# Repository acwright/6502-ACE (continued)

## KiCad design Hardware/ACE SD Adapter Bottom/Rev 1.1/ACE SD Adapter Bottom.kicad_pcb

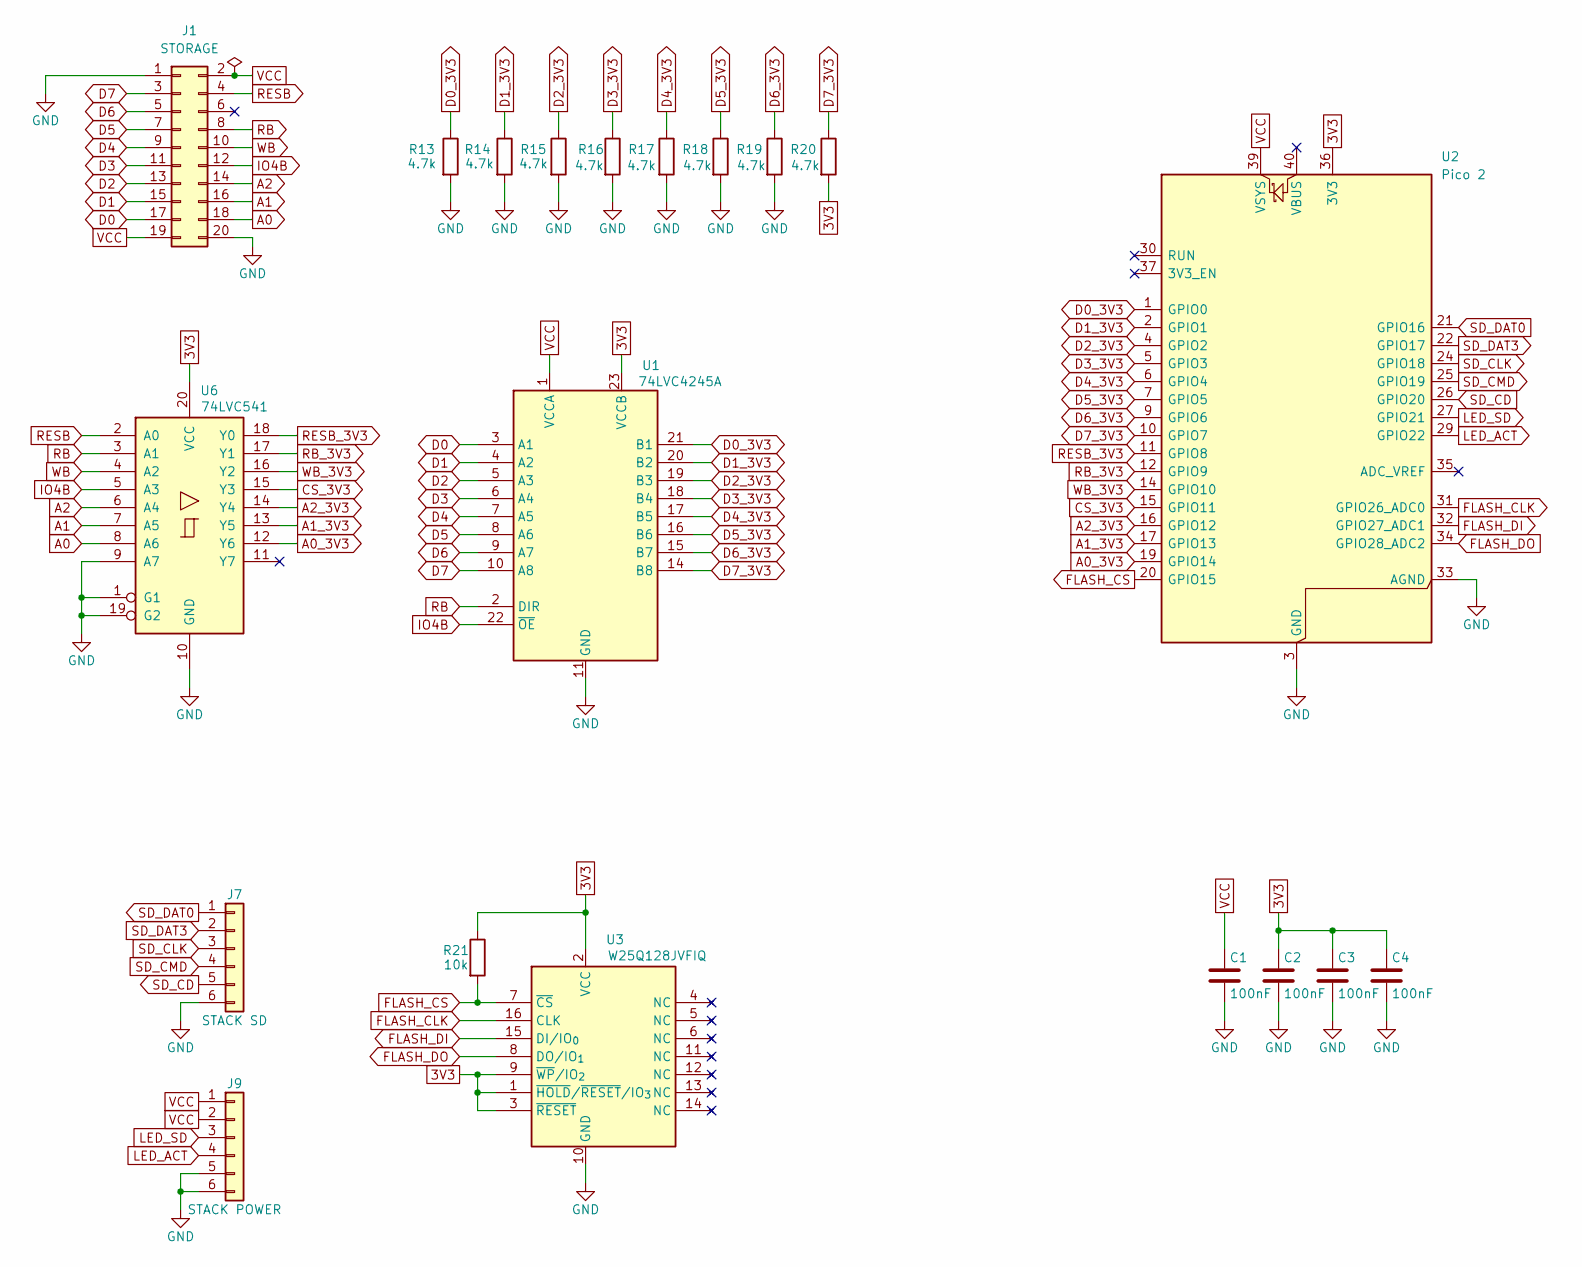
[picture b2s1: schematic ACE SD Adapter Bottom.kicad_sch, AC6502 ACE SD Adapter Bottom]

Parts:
C1, C2, C3, C4: 100nF; C_0805_2012Metric; Digikey 311-1140-1-ND
J1: STORAGE; PinHeader_2x10_P2.54mm_Horizontal; Digikey 609-3338-ND
J7: STACK SD; PinSocket_1x06_P2.54mm_Vertical; Digikey S7004-ND
J9: STACK POWER; PinSocket_1x06_P2.54mm_Vertical; Digikey S7004-ND
R13, R14, R15, R16, R17, R18, R19, R20: 4.7k; R_0805_2012Metric; Digikey 311-4.70KCRCT-ND
R21: 10k; R_0805_2012Metric; Digikey 311-10.0KCRCT-ND
U1: 74LVC4245A; TSSOP-24_4.4x7.8mm_P0.65mm; Digikey 296-12183-1-ND
U2: Pico 2; RaspberryPi_Pico_Common_THT; Digikey 2648-SC1631CT-ND
U3: W25Q128JVFIQ; SOIC-16W_7.5x10.3mm_P1.27mm; Digikey W25Q128JVFIQ-ND
U6: 74LVC541; TSSOP-20_4.4x6.5mm_P0.65mm; Digikey 1727-6370-1-ND

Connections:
3V3: C2.1, C3.1, C4.1, R20.2, R21.1, U1.23 (VCCB), U1.24 (VCCB), U2.36 (3V3), U3.1 (~HOLD/~RESET/IO_{3}), U3.2 (VCC), U3.3 (~RESET), U3.9 (~WP/IO_{2}), U6.20 (VCC)
A0: J1.18, U6.8 (A6)
A0_3V3: U2.19 (GPIO14), U6.12 (Y6)
A1: J1.16, U6.7 (A5)
A1_3V3: U2.17 (GPIO13), U6.13 (Y5)
A2: J1.14, U6.6 (A4)
A2_3V3: U2.16 (GPIO12), U6.14 (Y4)
CS_3V3: U2.15 (GPIO11), U6.15 (Y3)
D0: J1.17, U1.3 (A1)
D0_3V3: R13.1, U1.21 (B1), U2.1 (GPIO0)
D1: J1.15, U1.4 (A2)
D1_3V3: R14.1, U1.20 (B2), U2.2 (GPIO1)
D2: J1.13, U1.5 (A3)
D2_3V3: R15.1, U1.19 (B3), U2.4 (GPIO2)
D3: J1.11, U1.6 (A4)
D3_3V3: R16.1, U1.18 (B4), U2.5 (GPIO3)
D4: J1.9, U1.7 (A5)
D4_3V3: R17.1, U1.17 (B5), U2.6 (GPIO4)
D5: J1.7, U1.8 (A6)
D5_3V3: R18.1, U1.16 (B6), U2.7 (GPIO5)
D6: J1.5, U1.9 (A7)
D6_3V3: R19.1, U1.15 (B7), U2.9 (GPIO6)
D7: J1.3, U1.10 (A8)
D7_3V3: R20.1, U1.14 (B8), U2.10 (GPIO7)
FLASH_CLK: U2.31 (GPIO26_ADC0), U3.16 (CLK)
FLASH_CS: R21.2, U2.20 (GPIO15), U3.7 (~CS)
FLASH_DI: U2.32 (GPIO27_ADC1), U3.15 (DI/IO_{0})
FLASH_DO: U2.34 (GPIO28_ADC2), U3.8 (DO/IO_{1})
GND: C1.2, C2.2, C3.2, C4.2, J1.1, J1.20, J7.6, J9.5, J9.6, R13.2, R14.2, R15.2, R16.2, R17.2, R18.2, R19.2, U1.11 (GND), U1.12 (GND), U1.13 (GND), U2.3 (GND), U2.8 (GND), U2.13 (GND), U2.18 (GND), U2.23 (GND), U2.28 (GND), U2.33 (AGND), U2.38 (GND), U3.10 (GND), U6.1 (G1), U6.9 (A7), U6.10 (GND), U6.19 (G2)
IO4B: J1.12, U1.22 (~OE), U6.5 (A3)
LED_ACT: J9.4, U2.29 (GPIO22)
LED_SD: J9.3, U2.27 (GPIO21)
RB: J1.8, U1.2 (DIR), U6.3 (A1)
RB_3V3: U2.12 (GPIO9), U6.17 (Y1)
RESB: J1.4, U6.2 (A0)
RESB_3V3: U2.11 (GPIO8), U6.18 (Y0)
SD_CD: J7.5, U2.26 (GPIO20)
SD_CLK: J7.3, U2.24 (GPIO18)
SD_CMD: J7.4, U2.25 (GPIO19)
SD_DAT0: J7.1, U2.21 (GPIO16)
SD_DAT3: J7.2, U2.22 (GPIO17)
VCC: C1.1, J1.2, J1.19, J9.1, J9.2, U1.1 (VCCA), U2.39 (VSYS)
WB: J1.10, U6.4 (A2)
WB_3V3: U2.14 (GPIO10), U6.16 (Y2)

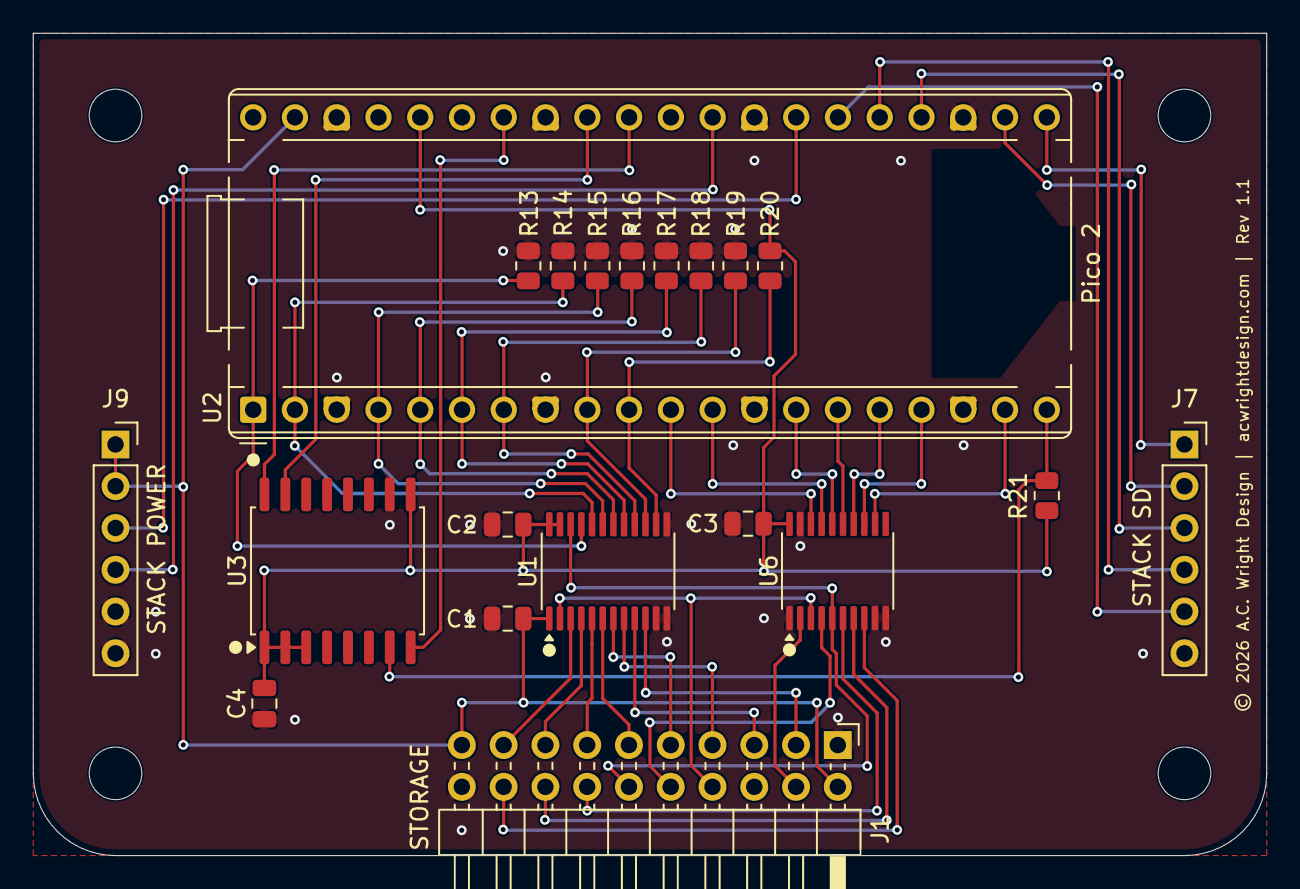
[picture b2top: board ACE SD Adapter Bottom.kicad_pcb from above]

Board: 2 copper layers, 75.0 x 50.0 mm, 20 parts (0 on the bottom side), 44 nets.

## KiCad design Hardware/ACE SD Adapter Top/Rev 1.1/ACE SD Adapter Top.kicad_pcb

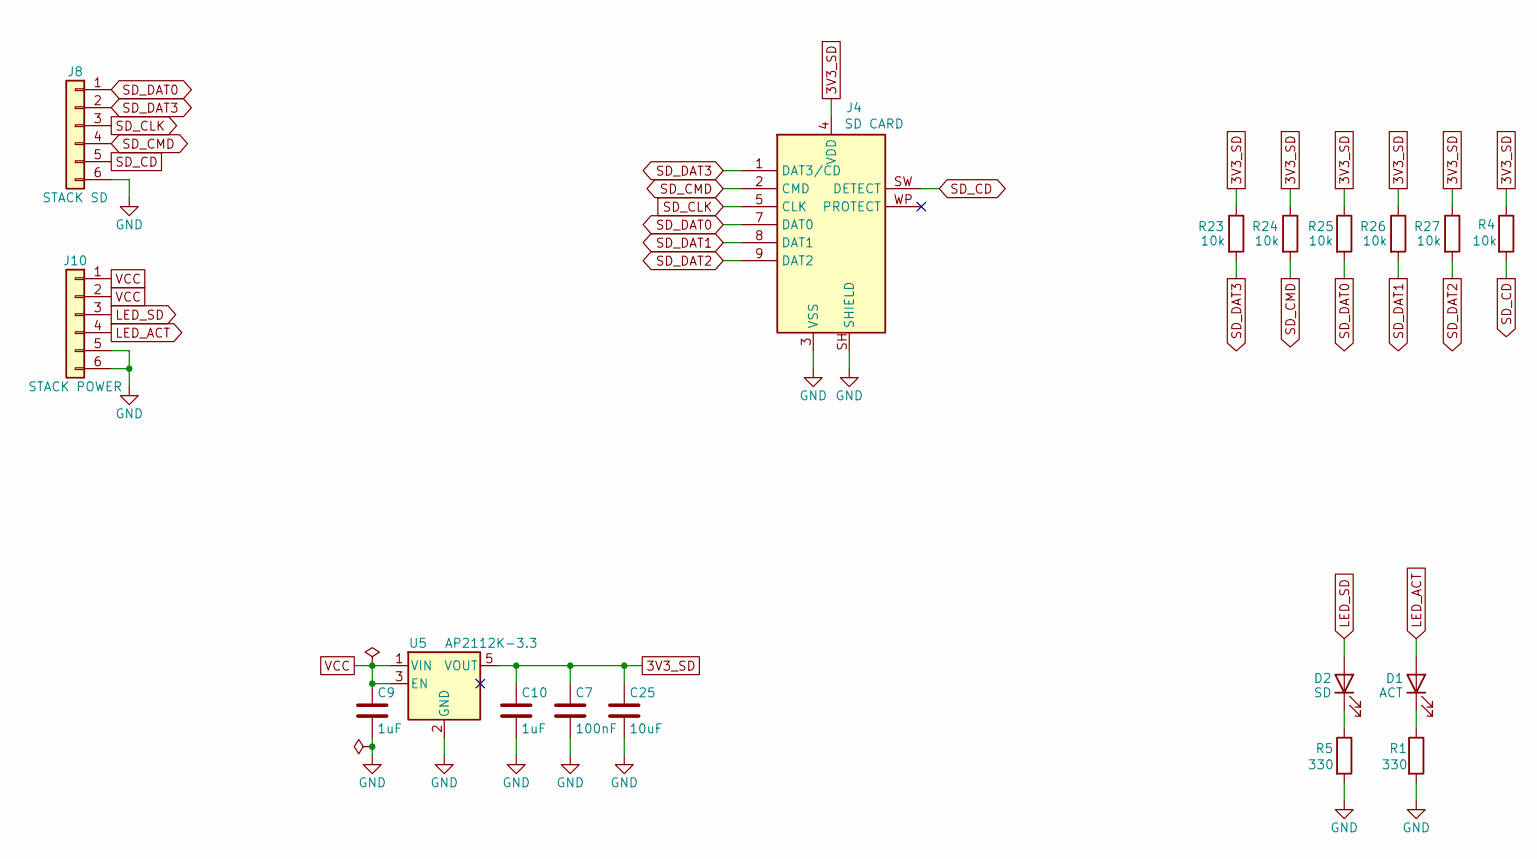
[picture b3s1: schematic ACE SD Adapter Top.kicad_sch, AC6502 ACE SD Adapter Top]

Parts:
C7: 100nF; C_0805_2012Metric; Digikey 311-1140-1-ND
C9, C10: 1uF; C_0805_2012Metric; Digikey 311-1456-1-ND
C25: 10uF; C_0805_2012Metric; Digikey 1276-CL21A106KAYNNNECT-ND
D1: ACT; LED_0805_2012Metric; Digikey 160-1415-1-ND
D2: SD; LED_0805_2012Metric; Digikey 160-1414-1-ND
J4: SD CARD; SD Card Socket Push-Push; LCSC C266603
J8: STACK SD; PinHeader_1x06_P2.54mm_Vertical; Digikey S1011EC-40-ND
J10: STACK POWER; PinHeader_1x06_P2.54mm_Vertical; Digikey S1011EC-40-ND
R1, R5: 330; R_0805_2012Metric; Digikey 311-330CRCT-ND
R4, R23, R24, R25, R26, R27: 10k; R_0805_2012Metric; Digikey 311-10.0KCRCT-ND
U5: AP2112K-3.3; SOT-23-5; Digikey AP2112K-3.3TRG1DICT-ND

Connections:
3V3_SD: C7.1, C10.1, C25.1, J4.4 (VDD), R4.1, R23.1, R24.1, R25.1, R26.1, R27.1, U5.5 (VOUT)
GND: C7.2, C9.2, C10.2, C25.2, J4.3 (VSS), J4.6 (VSS), J4.SH (SHIELD), J8.6, J10.5, J10.6, R1.2, R5.2, U5.2 (GND)
LED_ACT: D1.2 (A), J10.4
LED_SD: D2.2 (A), J10.3
unnamed: D1.1 (K), R1.1
unnamed: D2.1 (K), R5.1
SD_CD: J4.SW (DETECT), J8.5, R4.2
SD_CLK: J4.5 (CLK), J8.3
SD_CMD: J4.2 (CMD), J8.4, R24.2
SD_DAT0: J4.7 (DAT0), J8.1, R25.2
SD_DAT1: J4.8 (DAT1), R26.2
SD_DAT2: J4.9 (DAT2), R27.2
SD_DAT3: J4.1 (DAT3/CD), J8.2, R23.2
VCC: C9.1, J10.1, J10.2, U5.1 (VIN), U5.3 (EN)

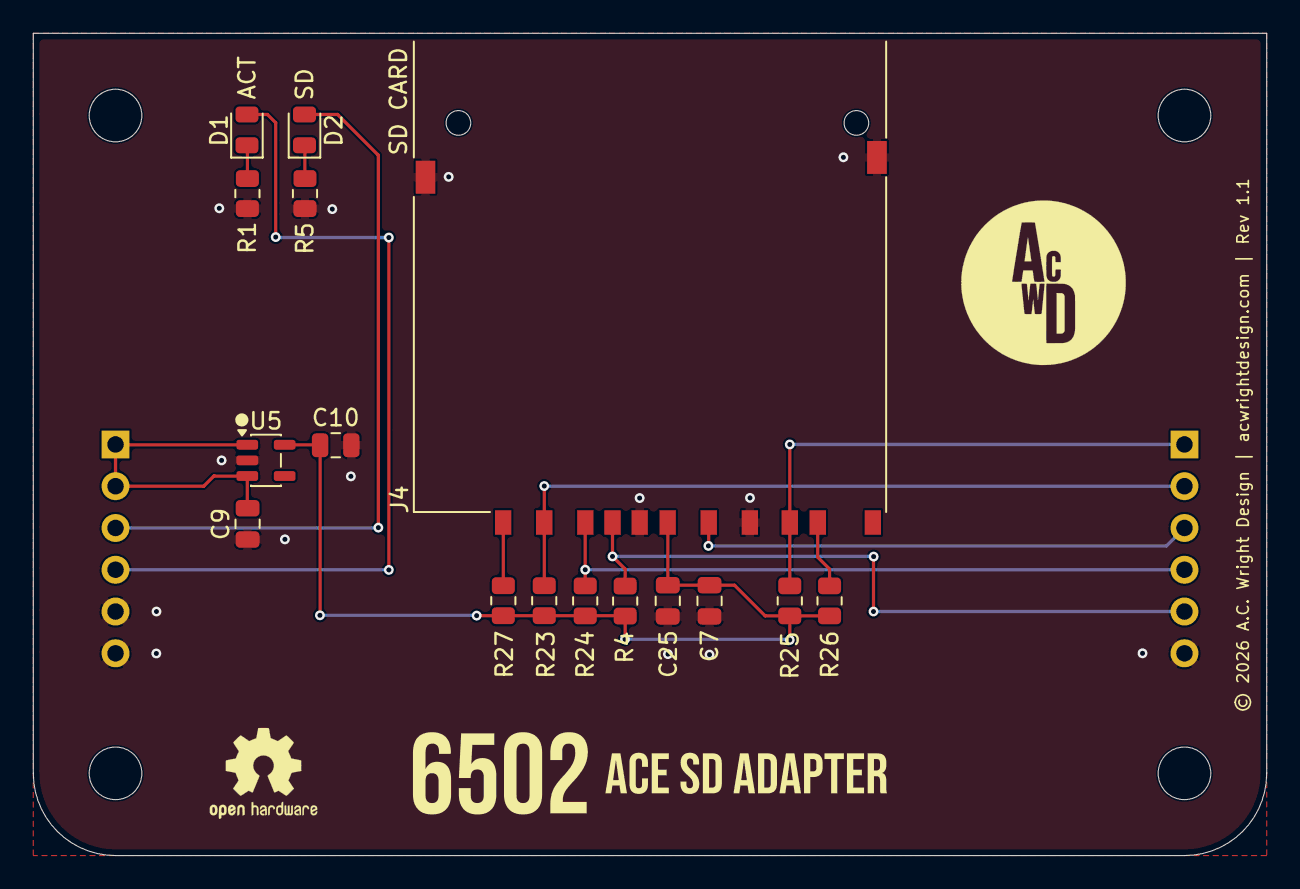
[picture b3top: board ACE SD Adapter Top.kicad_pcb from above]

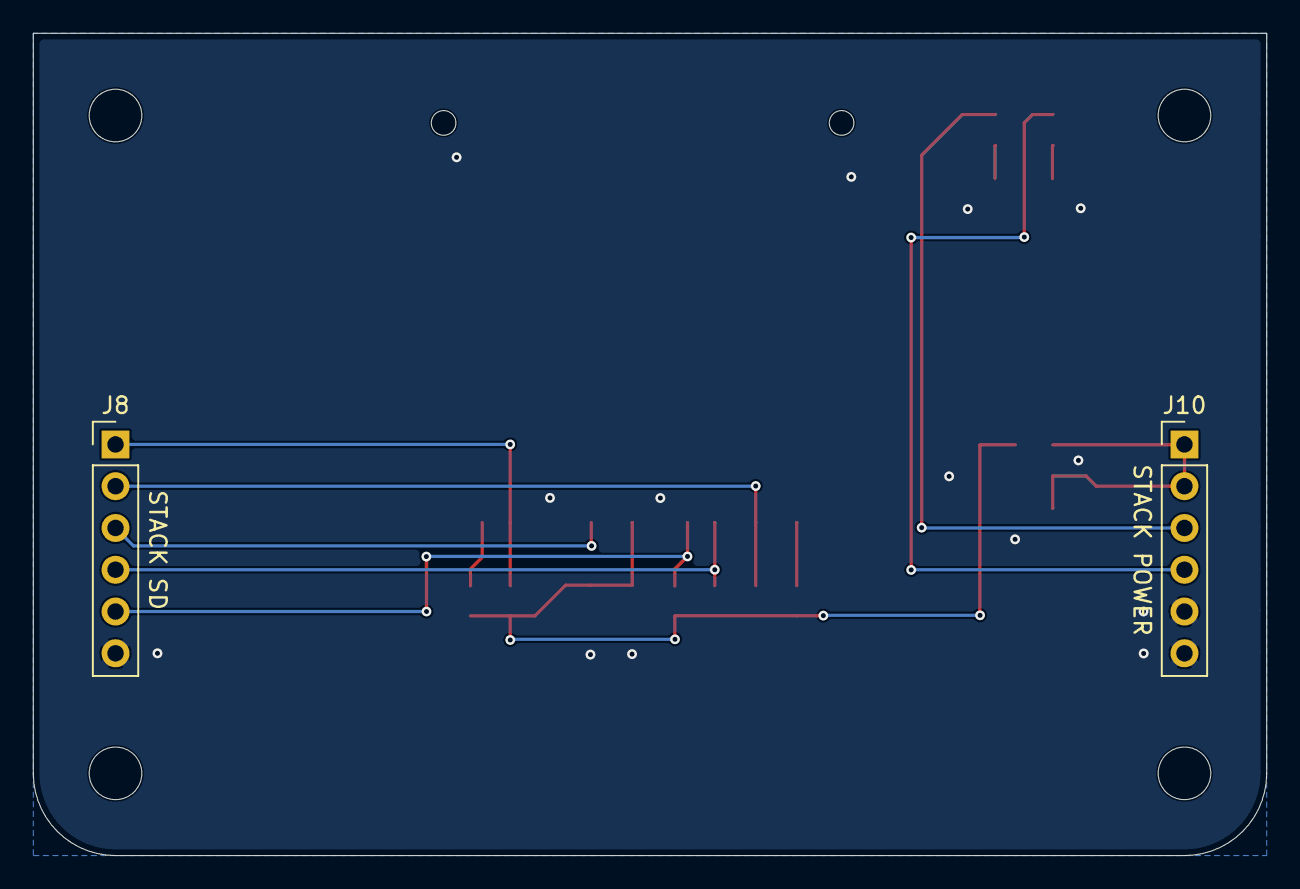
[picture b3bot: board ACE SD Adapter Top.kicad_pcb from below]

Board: 2 copper layers, 75.0 x 50.0 mm, 18 parts (2 on the bottom side), 14 nets.

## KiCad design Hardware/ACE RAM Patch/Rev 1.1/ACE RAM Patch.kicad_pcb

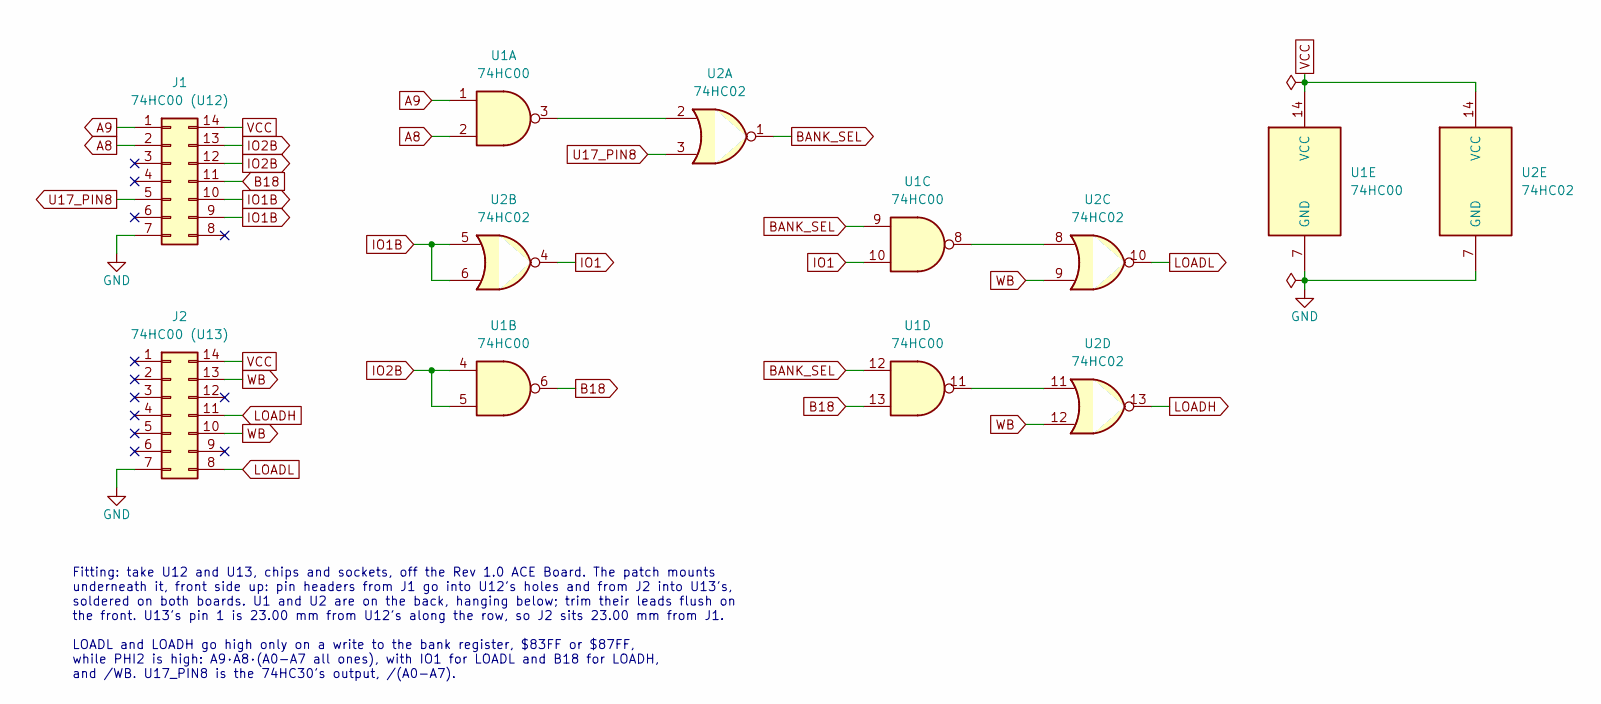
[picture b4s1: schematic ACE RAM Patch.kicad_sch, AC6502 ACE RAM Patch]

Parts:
J1: 74HC00 (U12); DIP-14_W7.62mm_LongPads; Digikey ED7264-64-ND
J2: 74HC00 (U13); DIP-14_W7.62mm_LongPads; Digikey ED7264-64-ND
U1: 74HC00; DIP-14_W7.62mm_LongPads; Digikey 296-1563-5-ND
U2: 74HC02; DIP-14_W7.62mm_LongPads; Digikey 296-1564-5-ND

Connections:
A8: J1.2, U1.2
A9: J1.1, U1.1
B18: J1.11, U1.6, U1.13
BANK_SEL: U1.9, U1.12, U2.1
GND: J1.7, J2.7, U1.7 (GND), U2.7 (GND)
IO1: U1.10, U2.4
IO1B: J1.9, J1.10, U2.5, U2.6
IO2B: J1.12, J1.13, U1.4, U1.5
LOADH: J2.11, U2.13
LOADL: J2.8, U2.10
unnamed: U1.3, U2.2
unnamed: U1.8, U2.8
unnamed: U1.11, U2.11
U17_PIN8: J1.5, U2.3
VCC: J1.14, J2.14, U1.14 (VCC), U2.14 (VCC)
WB: J2.10, J2.13, U2.9, U2.12

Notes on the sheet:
Fitting: take U12 and U13, chips and sockets, off the Rev 1.0 ACE Board. The patch mounts underneath it, front side up: pin headers from J1 go into U12's holes and from J2 into U13's, soldered on both boards. U1 and U2 are on the back, hanging below; trim their leads flush on the front. U13's pin 1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

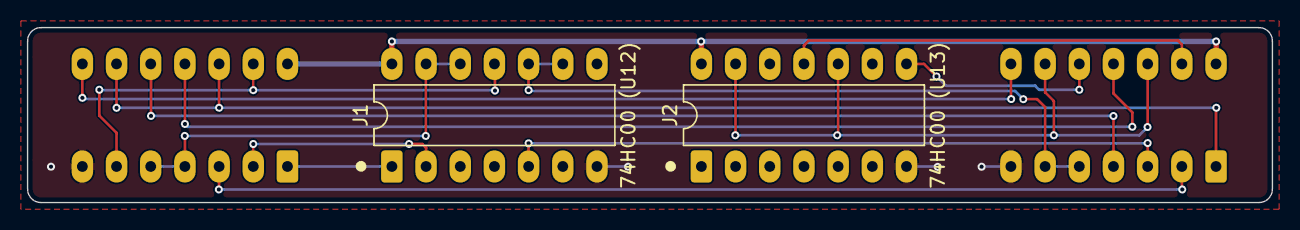
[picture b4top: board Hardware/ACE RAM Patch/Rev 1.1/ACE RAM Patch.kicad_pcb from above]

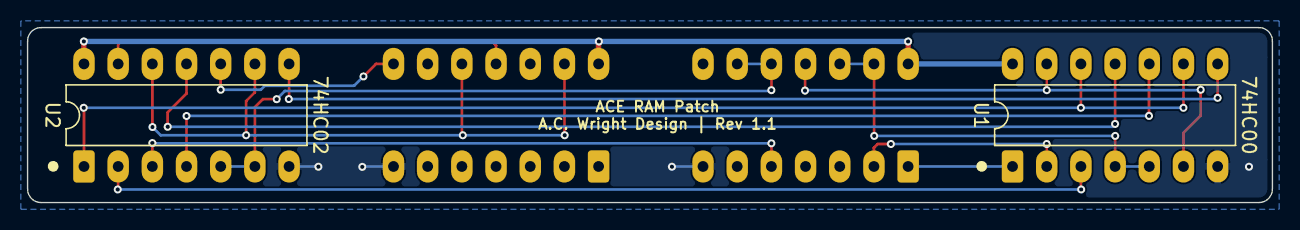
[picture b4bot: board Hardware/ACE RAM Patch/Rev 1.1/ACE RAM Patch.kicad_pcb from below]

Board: 2 copper layers, 92.5 x 13.0 mm, 4 parts (2 on the bottom side), 16 nets.

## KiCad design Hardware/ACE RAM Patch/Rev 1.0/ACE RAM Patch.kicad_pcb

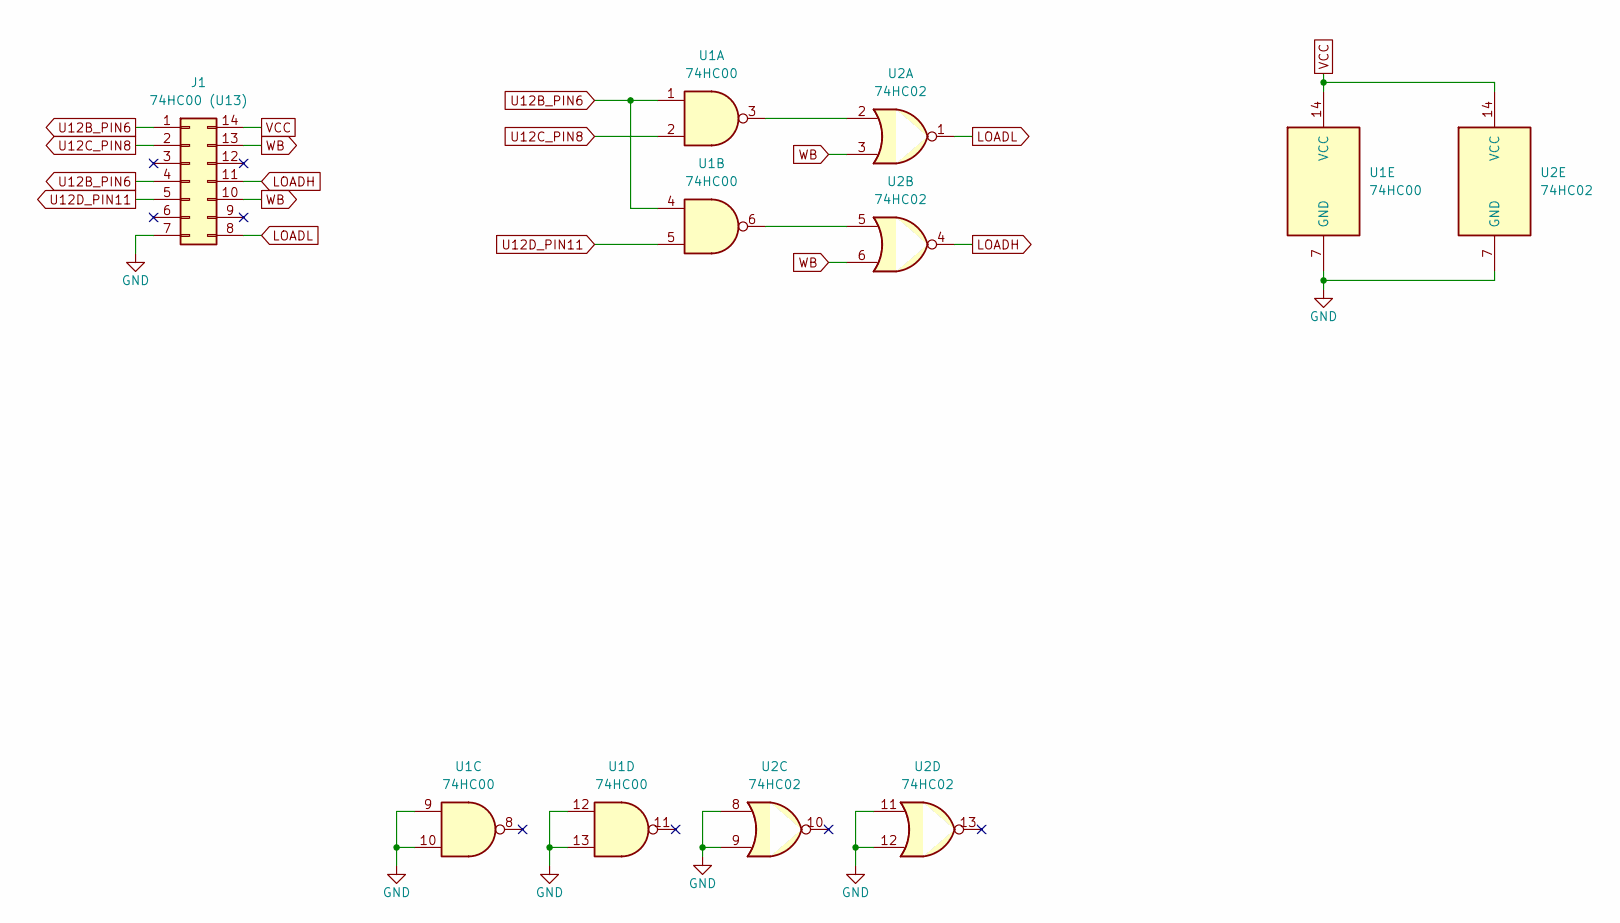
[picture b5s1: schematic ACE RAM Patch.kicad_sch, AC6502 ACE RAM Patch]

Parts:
J1: 74HC00 (U13); DIP-14_W7.62mm_LongPads; Digikey ED7264-64-ND
U1: 74HC00; DIP-14_W7.62mm_LongPads; Digikey 296-1563-5-ND
U2: 74HC02; DIP-14_W7.62mm_LongPads; Digikey 296-1564-5-ND

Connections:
GND: J1.7, U1.7 (GND), U1.9, U1.10, U1.12, U1.13, U2.7 (GND), U2.8, U2.9, U2.11, U2.12
LOADH: J1.11, U2.4
LOADL: J1.8, U2.1
unnamed: U1.3, U2.2
unnamed: U1.6, U2.5
U12B_PIN6: J1.1, J1.4, U1.1, U1.4
U12C_PIN8: J1.2, U1.2
U12D_PIN11: J1.5, U1.5
VCC: J1.14, U1.14 (VCC), U2.14 (VCC)
WB: J1.10, J1.13, U2.3, U2.6

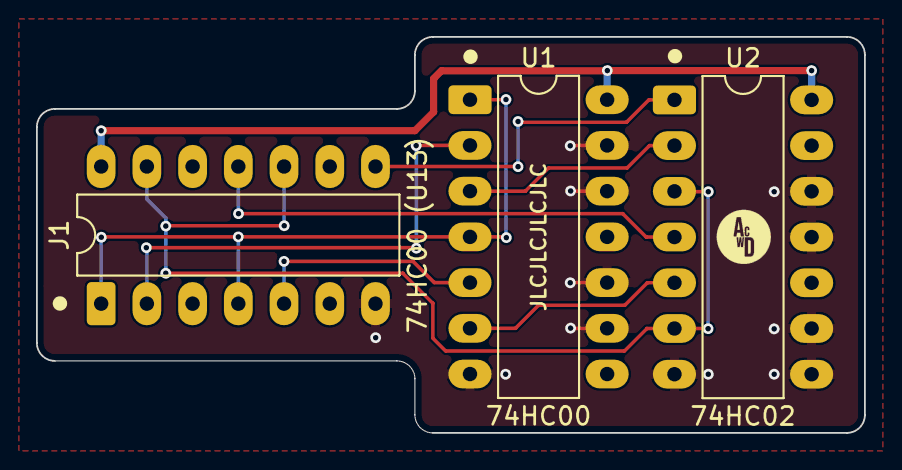
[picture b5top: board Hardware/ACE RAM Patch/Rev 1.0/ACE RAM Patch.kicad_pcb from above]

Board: 2 copper layers, 46.0 x 22.0 mm, 3 parts (0 on the bottom side), 10 nets.

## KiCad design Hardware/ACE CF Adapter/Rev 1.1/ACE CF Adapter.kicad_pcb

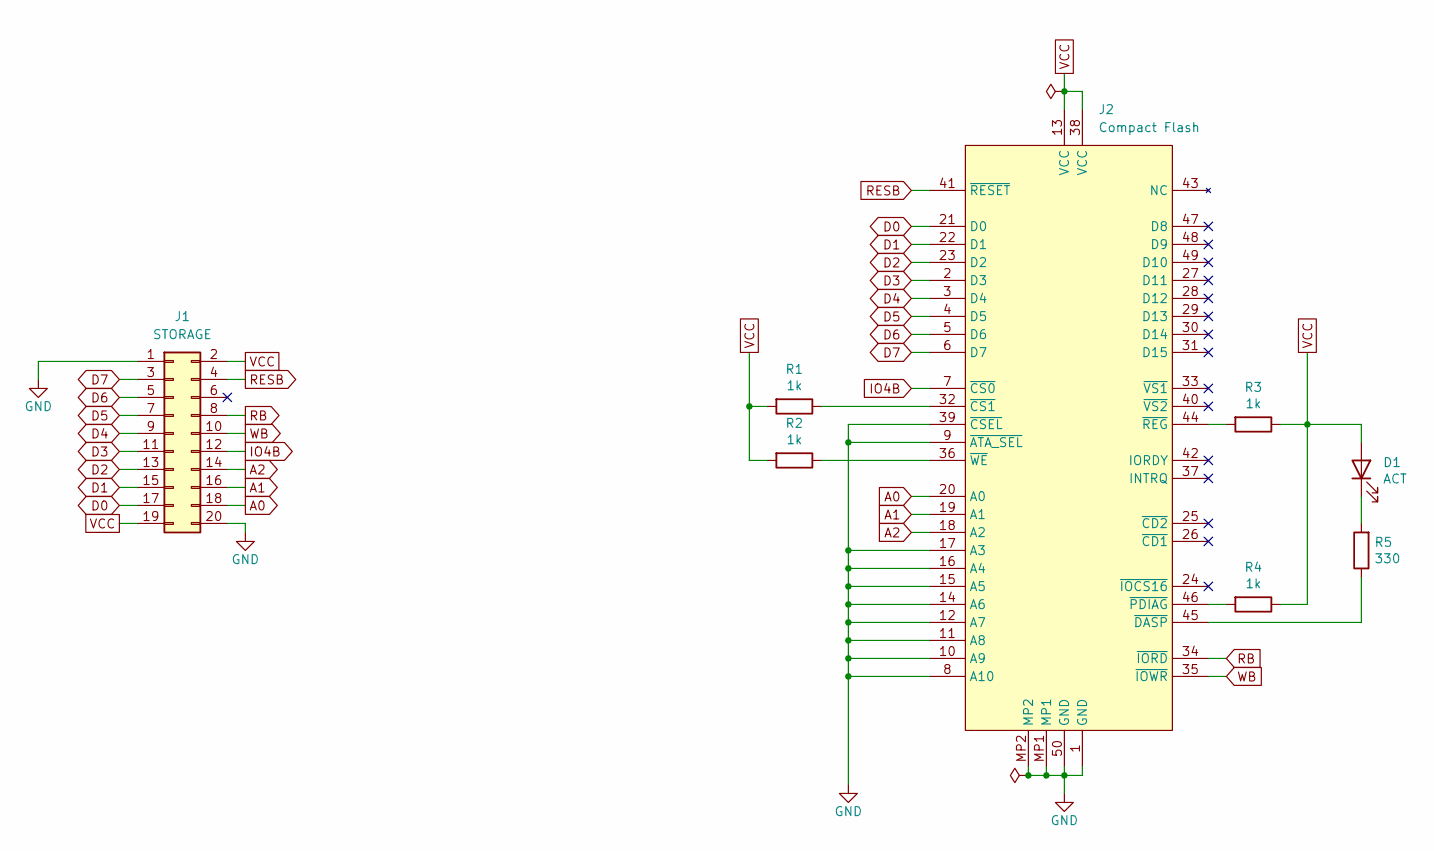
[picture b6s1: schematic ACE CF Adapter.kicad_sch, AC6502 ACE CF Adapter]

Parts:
D1: ACT; LED_0805_2012Metric; Digikey 160-1415-1-ND
J1: STORAGE; PinHeader_2x10_P2.54mm_Horizontal; Digikey 609-3338-ND
J2: Compact Flash; CompactFlash Socket; Digikey 4827-101D-TAAB-R01-ND
R1, R2, R3, R4: 1k; R_0805_2012Metric; Digikey 311-1.00KCRCT-ND
R5: 330; R_0805_2012Metric; Mouser 603-RC0805FR-07330RL

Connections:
A0: J1.18, J2.20 (A0)
A1: J1.16, J2.19 (A1)
A2: J1.14, J2.18 (A2)
D0: J1.17, J2.21 (D0)
D1: J1.15, J2.22 (D1)
D2: J1.13, J2.23 (D2)
D3: J1.11, J2.2 (D3)
D4: J1.9, J2.3 (D4)
D5: J1.7, J2.4 (D5)
D6: J1.5, J2.5 (D6)
D7: J1.3, J2.6 (D7)
GND: J1.1, J1.20, J2.1 (GND), J2.8 (A10), J2.9 (~ATA_SEL), J2.10 (A9), J2.11 (A8), J2.12 (A7), J2.14 (A6), J2.15 (A5), J2.16 (A4), J2.17 (A3), J2.39 (~CSEL), J2.50 (GND), J2.MP1, J2.MP2
IO4B: J1.12, J2.7 (~CS0)
unnamed: D1.1 (K), R5.2
unnamed: J2.32 (~CS1), R1.1
unnamed: J2.45 (~DASP), R5.1
unnamed: J2.46 (~PDIAG), R4.2
unnamed: J2.44 (~REG), R3.2
unnamed: J2.36 (~WE), R2.1
RB: J1.8, J2.34 (~IORD)
RESB: J1.4, J2.41 (~RESET)
VCC: D1.2 (A), J1.2, J1.19, J2.13 (VCC), J2.38 (VCC), R1.2, R2.2, R3.1, R4.1
WB: J1.10, J2.35 (~IOWR)

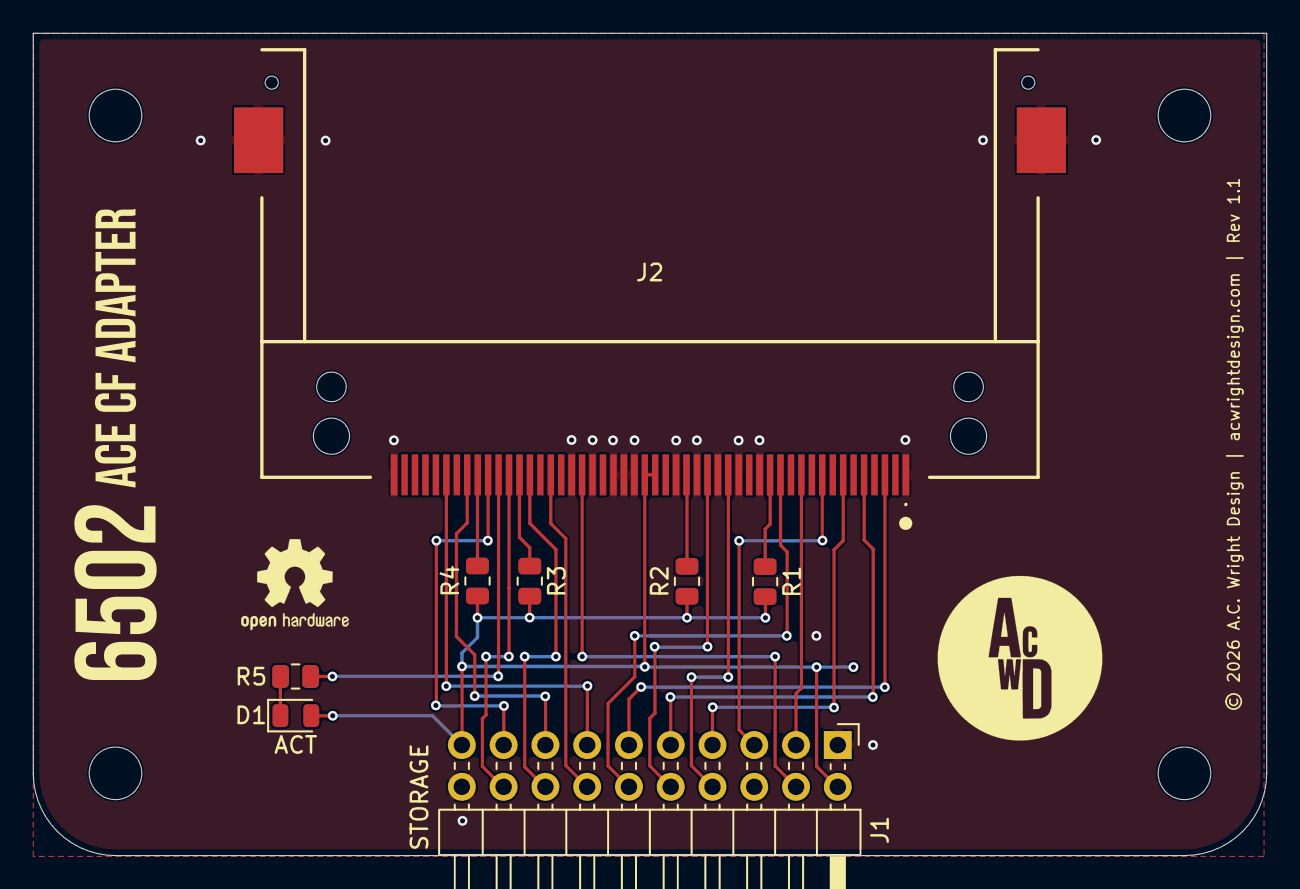
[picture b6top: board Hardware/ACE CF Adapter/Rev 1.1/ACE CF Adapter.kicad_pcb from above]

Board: 2 copper layers, 75.0 x 50.0 mm, 8 parts (0 on the bottom side), 23 nets.

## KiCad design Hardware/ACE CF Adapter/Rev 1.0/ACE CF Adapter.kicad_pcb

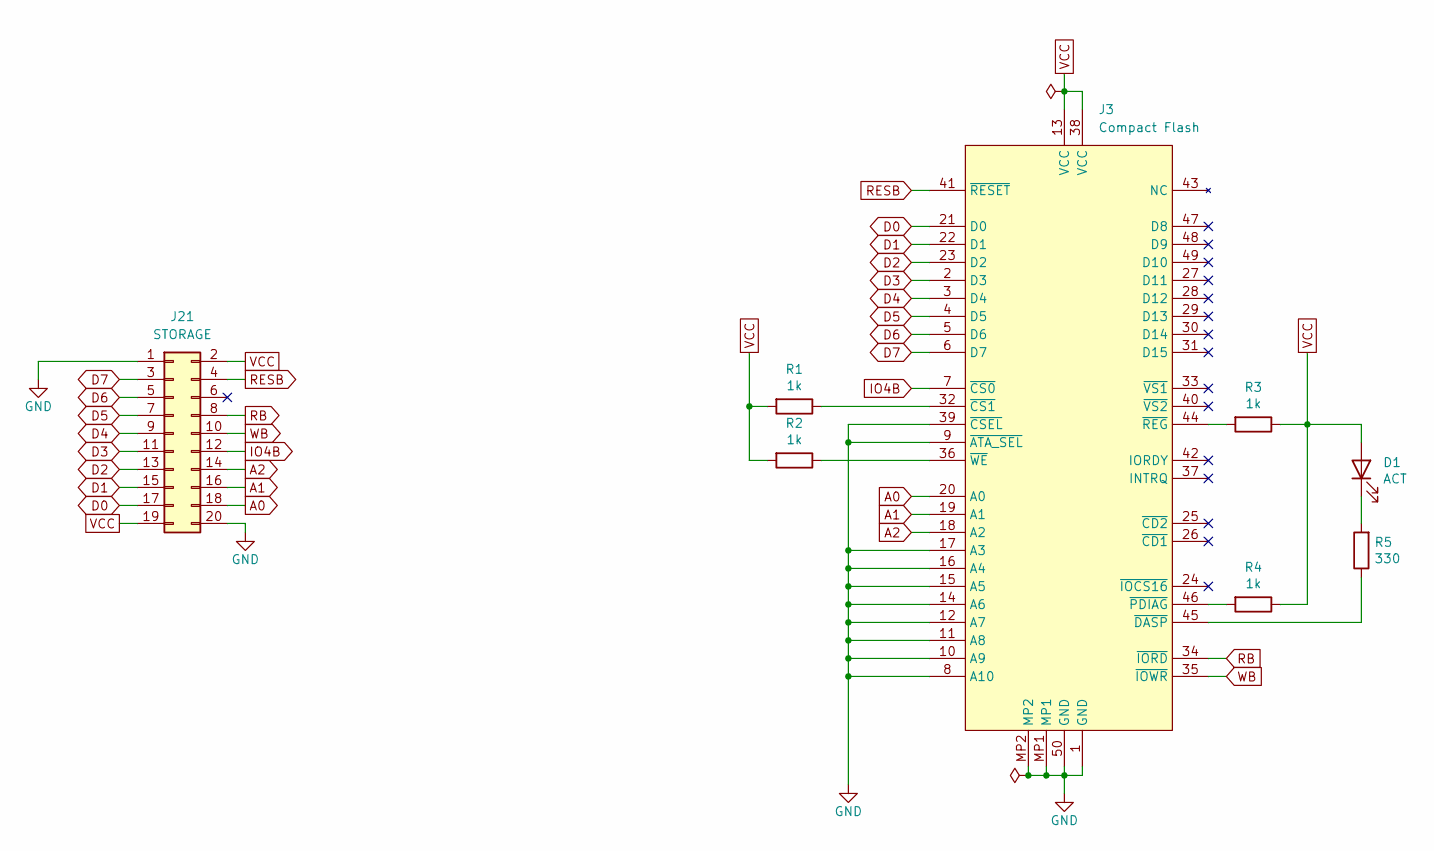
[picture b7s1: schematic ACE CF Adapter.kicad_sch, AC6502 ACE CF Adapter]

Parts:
D1: ACT; LED_D3.0mm; Digikey 732-5008-ND
J3: Compact Flash; CompactFlash Socket; Digikey 4827-101D-TAAB-R01-ND
J21: STORAGE; PinHeader_2x10_P2.54mm_Horizontal; Digikey 609-3338-ND
R1, R2, R3, R4: 1k; R_Axial_DIN0204_L3.6mm_D1.6mm_P5.08mm_Horizontal; Digikey 13-MFR-12FTF52-1KCT-ND
R5: 330; R_Axial_DIN0204_L3.6mm_D1.6mm_P5.08mm_Horizontal; Mouser 603-MFR-12FTF52-330R

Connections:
A0: J3.20 (A0), J21.18
A1: J3.19 (A1), J21.16
A2: J3.18 (A2), J21.14
D0: J3.21 (D0), J21.17
D1: J3.22 (D1), J21.15
D2: J3.23 (D2), J21.13
D3: J3.2 (D3), J21.11
D4: J3.3 (D4), J21.9
D5: J3.4 (D5), J21.7
D6: J3.5 (D6), J21.5
D7: J3.6 (D7), J21.3
GND: J3.1 (GND), J3.8 (A10), J3.9 (~ATA_SEL), J3.10 (A9), J3.11 (A8), J3.12 (A7), J3.14 (A6), J3.15 (A5), J3.16 (A4), J3.17 (A3), J3.39 (~CSEL), J3.50 (GND), J3.MP1, J3.MP2, J21.1, J21.20
IO4B: J3.7 (~CS0), J21.12
unnamed: D1.1 (K), R5.2
unnamed: J3.32 (~CS1), R1.1
unnamed: J3.45 (~DASP), R5.1
unnamed: J3.46 (~PDIAG), R4.2
unnamed: J3.44 (~REG), R3.2
unnamed: J3.36 (~WE), R2.1
RB: J3.34 (~IORD), J21.8
RESB: J3.41 (~RESET), J21.4
VCC: D1.2 (A), J3.13 (VCC), J3.38 (VCC), J21.2, J21.19, R1.2, R2.2, R3.1, R4.1
WB: J3.35 (~IOWR), J21.10

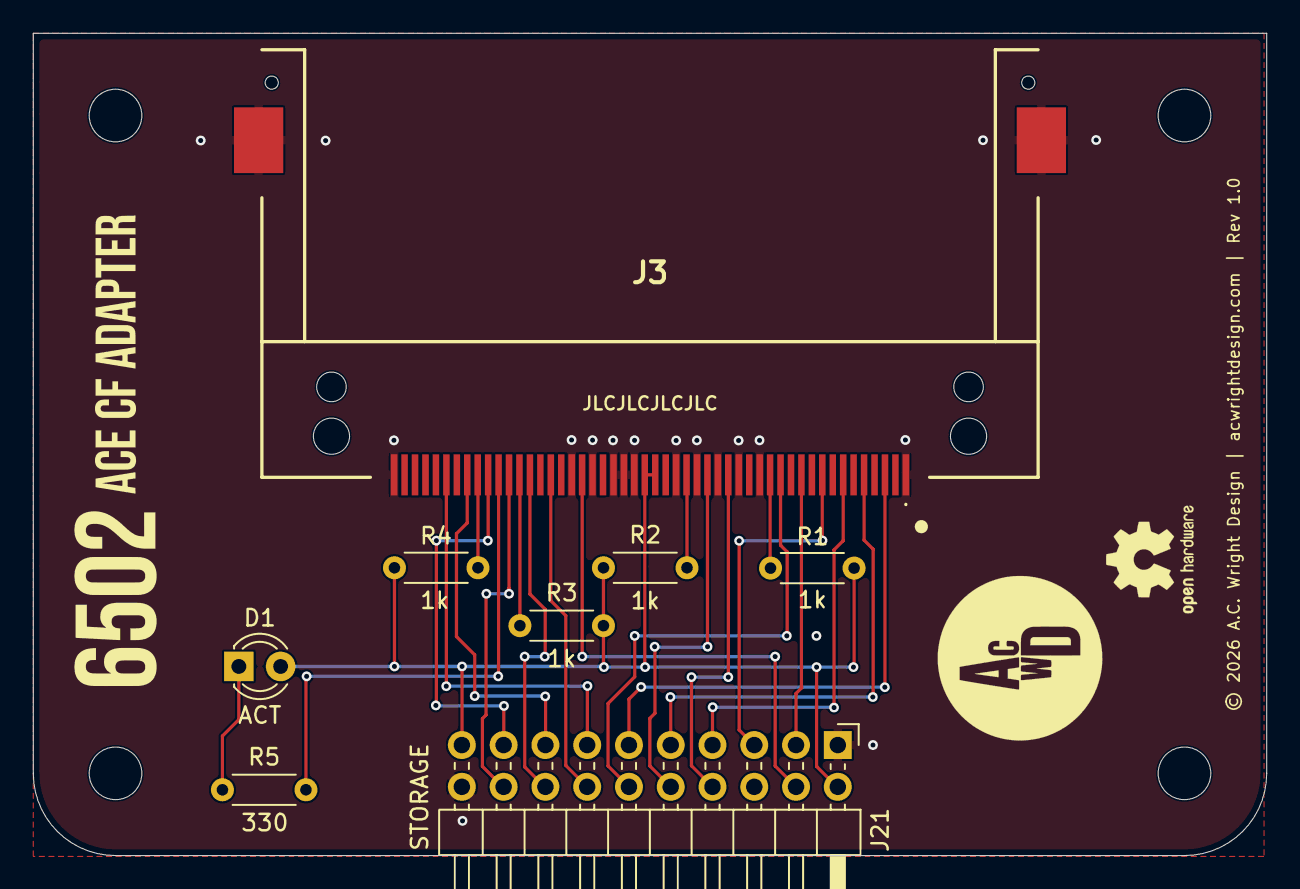
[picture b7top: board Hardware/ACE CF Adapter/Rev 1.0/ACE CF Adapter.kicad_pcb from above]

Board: 2 copper layers, 75.0 x 50.0 mm, 8 parts (0 on the bottom side), 23 nets.
